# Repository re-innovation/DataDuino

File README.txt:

The DataDuino is an Arduino based SD card datalogger.

The PedaLog was designed by Matt Little of www.re-innovation.co.uk
Contact: info@re-innovation.co.uk

The items in this repository include:

The PCB files were created in KiCAD PCB design software

Example code has been written for the Arduino IDE.

Example code for a serial-line monitoring datalogger code has also been included.

Overview of the design:

  A PCF8563 Realt Time Clock is used to timestamp the data.
  
  Pin D4 is set up to record a DS18B20 1 wire temp sensor (up to 4 sensors can be attached) 
  Pin D3 is set up to cound pulses from a sensor (such as a anemometer or flow sensor)
  Pins D7,D8,D9 are set up to record digital information (0 or 1)
  Pins A0 to A3 are set up to record analogue information (0 to 1024)
  
  Each logger has a reference (user adjustable from 00-99).
  
  Data is written to a .csv file created on an SD card.
  A new file is created each day. If file alreay present then data is appended.
  The file name is created from the reference number and the date in the format:
  RXXDXXXX.csv, where RXX is the reference number and DXXXX is the date in the format DDMM. 
  
  Data is stored with human readable headers:
  "Reference, Time, Date, Pulses, Temp1, Temp2, Temp3, Temp4, D7,D8,D9,A0,A1,A2,A3"
  
  You can adjust the parameters of the device using serial commands. These parameters are stored in EEPROM.
  These are:
  R??E
  This will change the reference number to ??
  T??????E
  This will change the time to HHMMSS
  D??????E
  This will change the date to DDMMYY
  S?????E
  This will change the sample period to ????? seconds. Set to 00001 for 1 second data, set to 03600 for 1 hour data.
  The minimum is 1 second data. The maximum is 99999 seconds

Modified:
23/9/13	GitHub Repository created - Matt Little

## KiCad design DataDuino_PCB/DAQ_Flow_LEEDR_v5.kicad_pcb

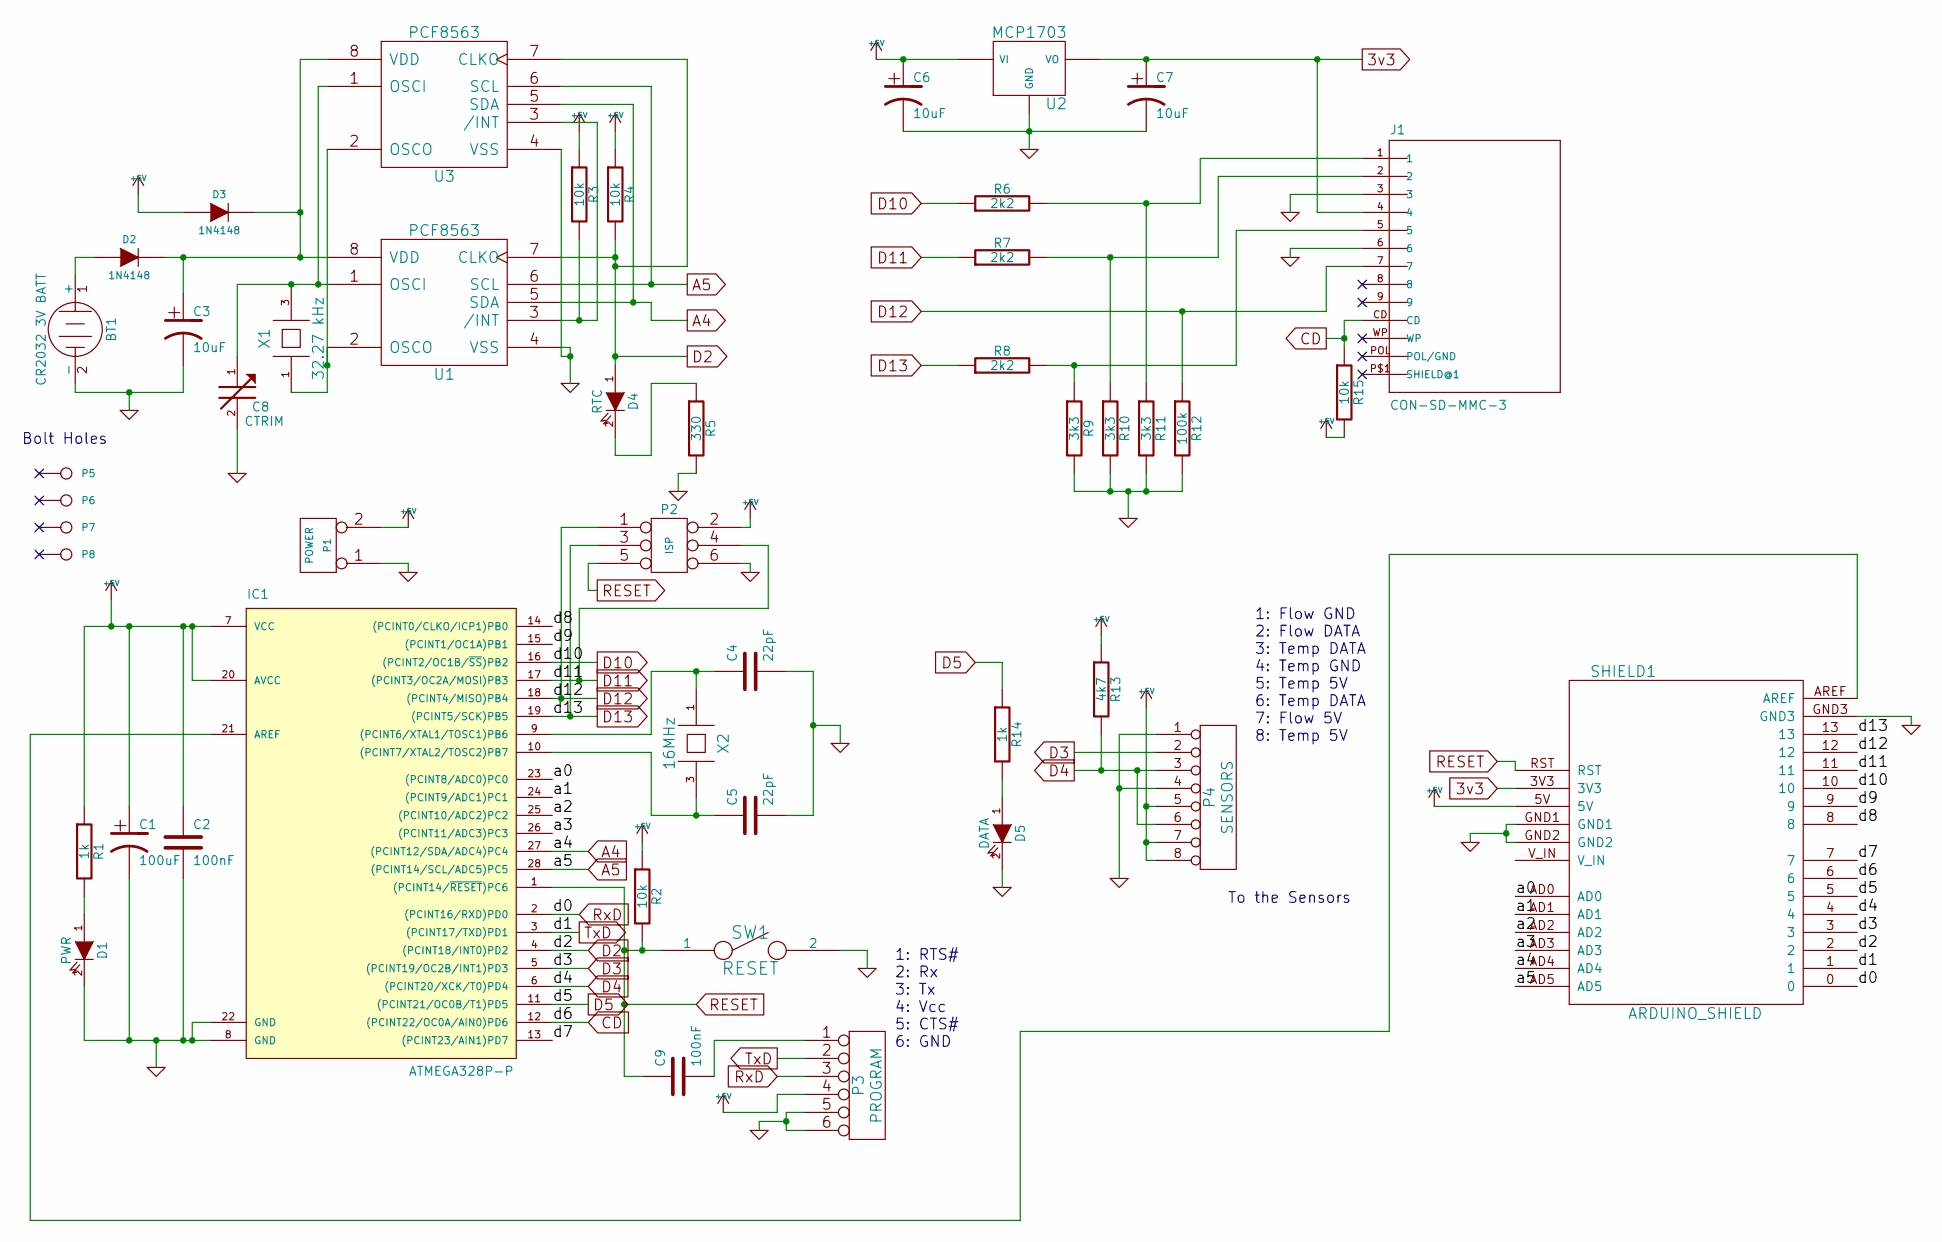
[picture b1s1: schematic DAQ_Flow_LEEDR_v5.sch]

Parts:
BT1: CR2032 3V BATT; Batt_conn_20mm_thruh
C1: 100uF; C2V8_large_pads
C2, C9: 100nF; C1_wide_lg_pad
C3, C6, C7: 10uF; C2V8_large_pad
C4, C5: 22pF; C1_lg_pad
C8: CTRIM; CTrim
D1: PWR; led-LED3MM_matt
D2, D3: 1N4148; D4_lg_pad
D4: RTC; led-LED3MM_matt
D5: DATA; led-LED3MM_matt
IC1: ATMEGA328P-P; DIP-28__300_ELL
J1: CON-SD-MMC-3; SD_holder_3M_matt
P1: POWER; Plug_power_5_3mm
P2: ISP; DIL_3x2_large_pads_1mm
P3: PROGRAM; SIL-6_large_pads_marker
P4: SENSORS; SIL-8_lg_pad_1mm
P5, P6, P7, P8: CONN_1; 3mm_hole
R1, R14: 1k; R3-LARGE_PADS_0_8_hole
R2, R3, R4, R15: 10k; R3-LARGE_PADS_0_8_hole
R5: 330; R3-LARGE_PADS_0_8_hole
R6, R7, R8: 2k2; R3-LARGE_PADS_0_8_hole
R9, R10, R11: 3k3; R3-LARGE_PADS_0_8_hole
R12: 100k; R3-LARGE_PADS_0_8_hole
R13: 4k7; R3-LARGE_PADS_0_8_hole
SHIELD1: ARDUINO_SHIELD; ARDUINO_SHIELD_040pins_no_hole_large_pad_no_outline
SW1: RESET; SW_PUSH_single_pins
U1: PCF8563; DIP-8_300_ELL
U2: MCP1703; TO92_MCP9701_matt_2
U3: PCF8563; SM_SOIC_8
X1: 32.27 kHz; Xtal_watch_matt
X2: 16MHz; Xtal_small_matt

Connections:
3v3: C7.1, J1.4, SHIELD1.3V3, U2.VO
+5V: C1.1, C2.1, C6.1, D3.1 (A), IC1.7 (VCC), IC1.20 (AVCC), P1.2 (PM), P2.2, P3.4, P4.5, P4.7, P4.8, R1.1, R2.1, R3.1, R4.1, R13.1, R15.2, SHIELD1.5V, U2.VI
/a0: IC1.23 ((PCINT8/ADC0)PC0), SHIELD1.AD0
/a1: IC1.24 ((PCINT9/ADC1)PC1), SHIELD1.AD1
/a2: IC1.25 ((PCINT10/ADC2)PC2), SHIELD1.AD2
/a3: IC1.26 ((PCINT11/ADC3)PC3), SHIELD1.AD3
/d7: IC1.13 ((PCINT23/AIN1)PD7), SHIELD1.7
/d8: IC1.14 ((PCINT0/CLKO/ICP1)PB0), SHIELD1.8
/d9: IC1.15 ((PCINT1/OC1A)PB1), SHIELD1.9
A4: IC1.27 ((PCINT12/SDA/ADC4)PC4), SHIELD1.AD4, U1.5 (SDA), U3.5 (SDA)
A5: IC1.28 ((PCINT14/SCL/ADC5)PC5), SHIELD1.AD5, U1.6 (SCL), U3.6 (SCL)
CD: IC1.12 ((PCINT22/OC0A/AIN0)PD6), J1.CD, R15.1, SHIELD1.6
D2: D4.1 (A), IC1.4 ((PCINT18/INT0)PD2), R4.2, SHIELD1.2, U1.7 (CLKO), U3.7 (CLKO)
D3: IC1.5 ((PCINT19/OC2B/INT1)PD3), P4.2, SHIELD1.3
D4: IC1.6 ((PCINT20/XCK/T0)PD4), P4.3, P4.6, R13.2, SHIELD1.4
D5: IC1.11 ((PCINT21/OC0B/T1)PD5), R14.1, SHIELD1.5
D10: IC1.16 ((PCINT2/OC1B/~SS~)PB2), R6.1, SHIELD1.10
D11: IC1.17 ((PCINT3/OC2A/MOSI)PB3), P2.4, R7.1, SHIELD1.11
D12: IC1.18 ((PCINT4/MISO)PB4), J1.7, P2.1, R12.1, SHIELD1.12
D13: IC1.19 ((PCINT5/SCK)PB5), P2.3, R8.1, SHIELD1.13
GND: BT1.2 (-), C1.2, C2.2, C3.2, C4.2, C5.2, C6.2, C7.2, C8.2, D1.2 (K), D5.2 (K), IC1.8 (GND), IC1.22 (GND), J1.3, J1.6, P1.1, P2.6, P3.5, P3.6, P4.1, P4.4, R5.2, R9.2, R10.2, R11.2, R12.2, SHIELD1.GND1, SHIELD1.GND2, SHIELD1.GND3, SW1.2, U1.4 (VSS), U2.GND, U3.4 (VSS)
unnamed: BT1.1 (+), D2.1 (A)
unnamed: C3.1, D2.2 (K), D3.2 (K), U1.8 (VDD), U3.8 (VDD)
unnamed: C4.1, IC1.9 ((PCINT6/XTAL1/TOSC1)PB6), X2.1
unnamed: C5.1, IC1.10 ((PCINT7/XTAL2/TOSC2)PB7), X2.3
unnamed: C8.1, U1.1 (OSCI), U3.1 (OSCI), X1.3
unnamed: C9.2, P3.1
unnamed: D1.1 (A), R1.2
unnamed: D4.2 (K), R5.1
unnamed: D5.1 (A), R14.2
unnamed: IC1.21 (AREF), SHIELD1.AREF
unnamed: J1.1, R6.2, R11.1
unnamed: J1.2, R7.2, R10.1
unnamed: J1.5, R8.2, R9.1
unnamed: R3.2, U1.3 (/INT), U3.3 (/INT)
unnamed: U1.2 (OSCO), U3.2 (OSCO), X1.1
RESET: C9.1, IC1.1 ((PCINT14/~RESET~)PC6), P2.5, R2.2, SHIELD1.RST, SW1.1
RxD: IC1.2 ((PCINT16/RXD)PD0), P3.3, SHIELD1.0
TxD: IC1.3 ((PCINT17/TXD)PD1), P3.2, SHIELD1.1

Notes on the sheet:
Bolt Holes
1: RTS# 2: Rx 3: Tx 4: Vcc 5: CTS# 6: GND
1: Flow GND 2: Flow DATA 3: Temp DATA 4: Temp GND 5: Temp 5V 6: Temp DATA 7: Flow 5V 8: Temp 5V
To the Sensors

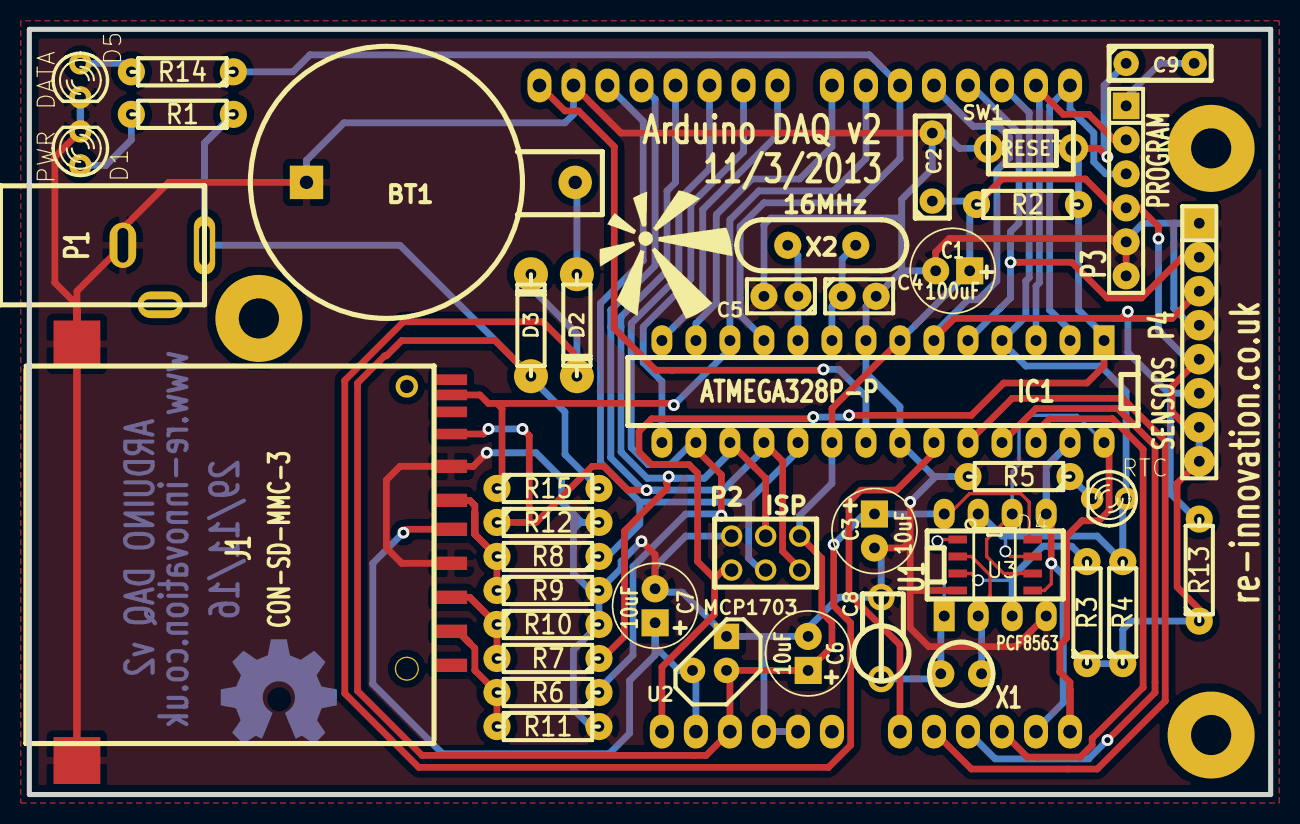
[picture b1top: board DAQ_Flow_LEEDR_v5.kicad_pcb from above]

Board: 2 copper layers, 92.7 x 57.1 mm, 48 parts (0 on the bottom side), 39 nets.

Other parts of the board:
VAL: OSHW_logo_small_back
VAL#2: reinnovation_logo_15mm

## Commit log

2013-09-23 second commit
2015-06-04 Arduino code update
    Arduino code working on IDE v 1.0.4
2015-06-04 Deleted old version
2018-12-30 Update of PCB files
